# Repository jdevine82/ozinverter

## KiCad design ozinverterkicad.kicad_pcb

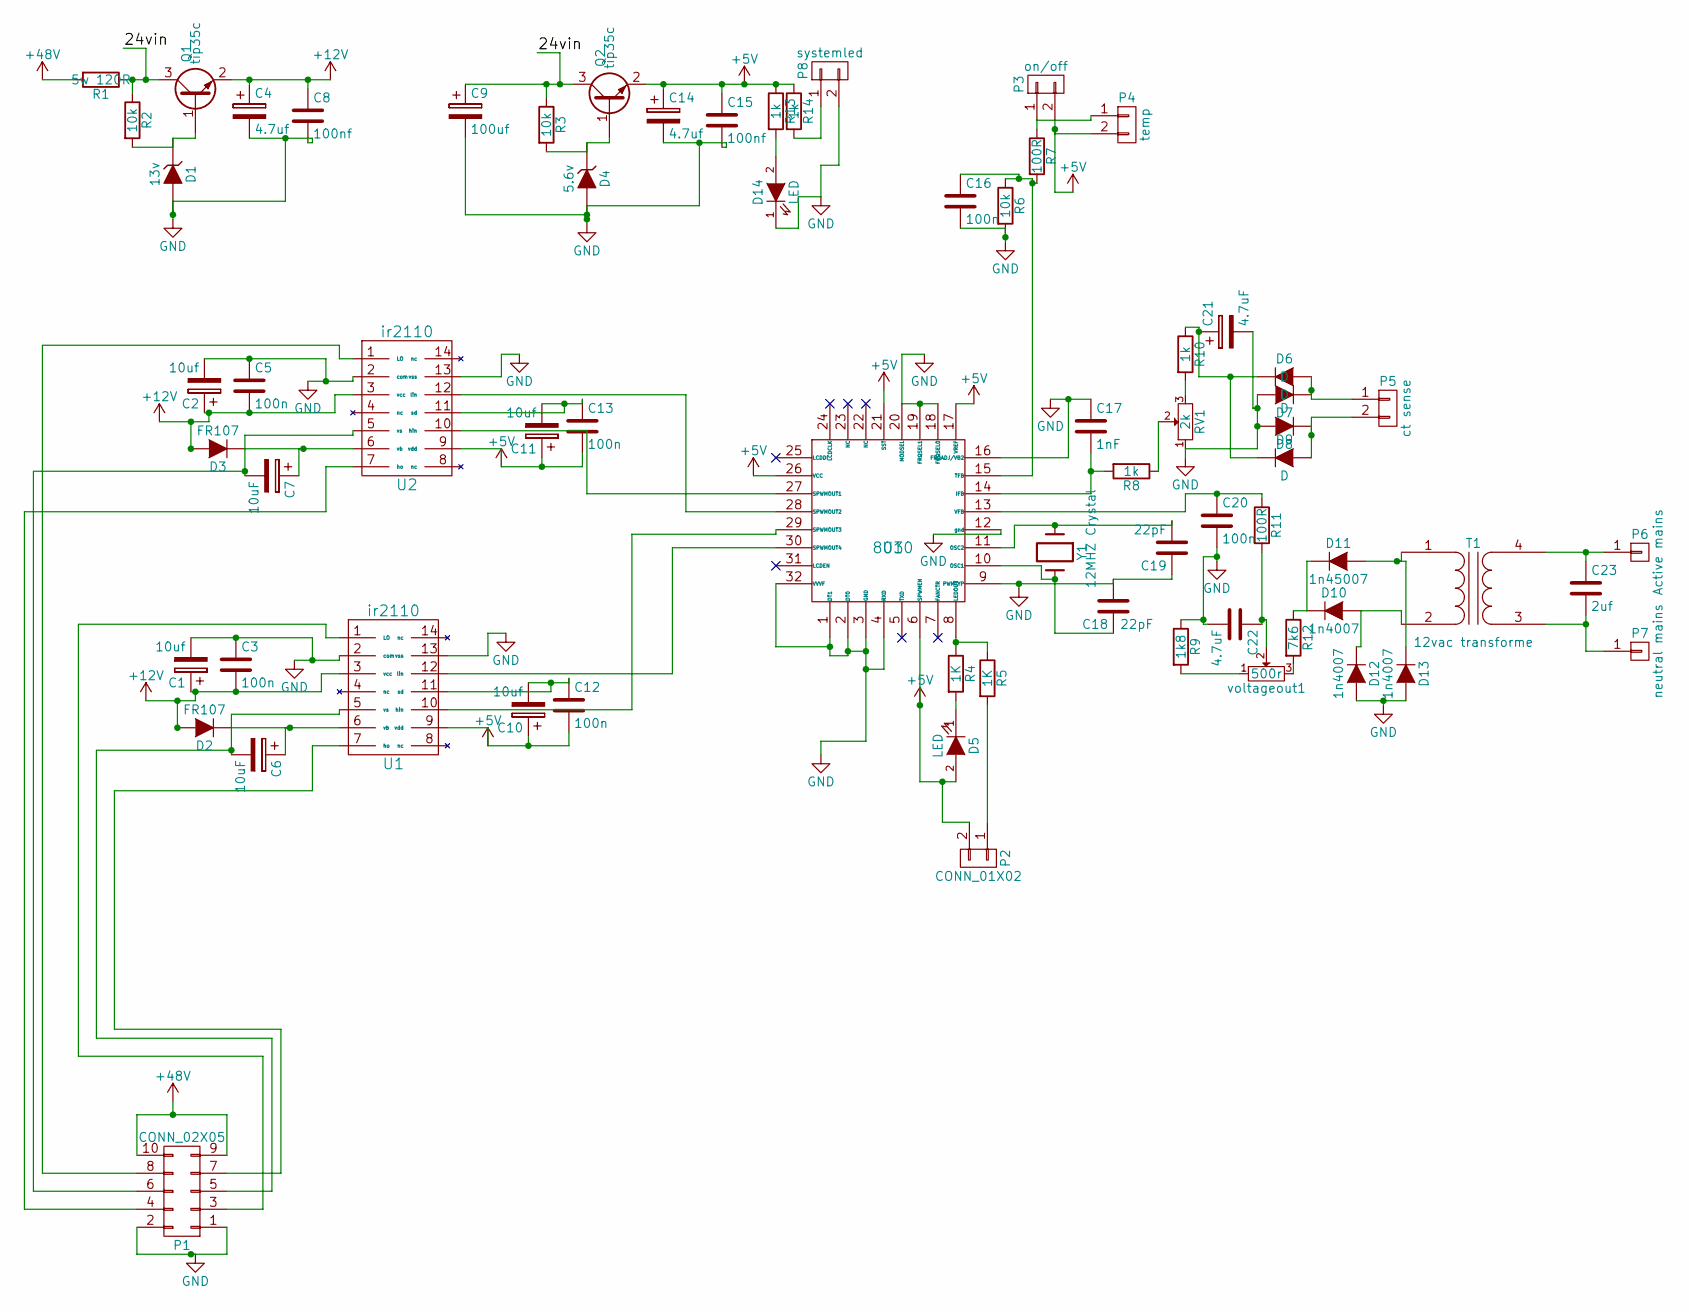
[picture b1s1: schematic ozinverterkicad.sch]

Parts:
C1, C2: 10uf; C_Radial_D5_L6_P2.5
C3, C5, C12, C13, C16, C20: 100n; C_Rect_L7_W2.5_P5
C4, C14: 4.7uf; C_Radial_D5_L6_P2.5
C6, C7: 10uF; C_Radial_D5_L6_P2.5
C8, C15: 100nf; C_Rect_L7_W2.5_P5
C9: 100uf; C_Radial_D6.3_L11.2_P2.5
C10, C11: 10uf; C_Radial_D5_L11_P2.5
C17: 1nF; C_Rect_L7_W2.5_P5
C18, C19: 22pF; C_Disc_D3_P2.5
C21, C22: 4.7uF; C_Radial_D5_L6_P2.5
C23: 2uf; C_Radial_D5_L6_P2.5
D1: 13v; Diode_DO-41_SOD81_Vertical_AnodeUp
D2, D3: FR107; Diode_DO-41_SOD81_Vertical_AnodeUp
D4: 5.6v; Diode_DO-41_SOD81_Vertical_AnodeUp
D5, D14: LED; LED-5MM
D6, D7, D8, D9: D; Diode_DO-41_SOD81_Vertical_AnodeUp
D10, D12, D13: 1n4007; Diode_DO-41_SOD81_Vertical_AnodeUp
D11: 1n45007; Diode_DO-41_SOD81_Vertical_AnodeUp
P1: CONN_02X05; IDC_Header_Straight_10pins
P2: CONN_01X02; Molex_KK-6410-02_02x2.54mm_Straight
P3: on/off; Molex_KK-6410-02_02x2.54mm_Straight
P4: temp; Molex_KK-6410-02_02x2.54mm_Straight
P5: ct sense; Molex_KK-6410-02_02x2.54mm_Straight
P6: Active mains; 1pin
P7: neutral mains; 1pin
P8: systemled; Molex_KK-6410-02_02x2.54mm_Straight
Q1, Q2: tip35c; TO-247_Vertical_Neutral123
R1: 5w 120R; Resistor_Horizontal_RM30mm
R2, R3, R6: 10k; Resistor_Horizontal_RM7mm
R4, R5: 1K; Resistor_Horizontal_RM7mm
R7, R11: 100R; Resistor_Horizontal_RM7mm
R8, R10, R13, R14: 1k; Resistor_Horizontal_RM7mm
R9: 1k8; Resistor_Horizontal_RM7mm
R12: 7k6; Resistor_Horizontal_RM7mm
RV1: 2k; RV2X4
T1: 12vac transforme; 3wtransformer
U1, U2: ir2110; DIP-14_W7.62mm
U3: 8010; DIP-32_W15.24mm
Y1: 12MHZ Crystal; Crystal_HC48-U_Vertical
voltageout1: 500r; RV2X4

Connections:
+5V: C10.1, C11.1, C12.2, C13.2, C14.1, C15.1, D5.2 (A), P2.2, P3.2, P4.2, Q2.2 (E), R13.1, R14.1, U1.9 (vdd), U2.9 (vdd), U3.6 (SPWMEN), U3.17 (VREF), U3.21 (SST), U3.26 (VCC)
+12V: C1.1, C2.1, C3.2, C4.1, C5.2, C8.1, D2.2 (A), D3.2 (A), Q1.2 (E), U1.3 (vcc), U2.3 (vcc)
+48V: P1.9, P1.10, R1.2
/24vin: C9.1, Q1.3 (C), Q2.3 (C), R1.1, R2.1, R3.1
GND: C1.2, C2.2, C3.1, C4.2, C5.1, C8.2, C9.2, C14.2, C15.2, C16.2, C17.1, C18.2, C19.1, C20.2, C21.2, C22.2, D1.2 (A), D4.2 (A), D7.2 (A), D8.2 (A), D12.2 (A), D13.2 (A), D14.1 (K), P1.1, P1.2, P8.2, R6.2, R9.1, RV1.1, U1.2 (com), U1.13 (vss), U2.2 (com), U2.13 (vss), U3.1 (DT1), U3.2 (DT0), U3.3 (GND), U3.4 (RXD), U3.9 (PWMTYP), U3.12 (gnd), U3.16 (FRQADJ/VB2), U3.18 (FRQSEL0), U3.19 (FRQSEL1), U3.20 (MODSEL), U3.32 (VVVF)
unnamed: C6.1, D2.1 (K), U1.6 (vb)
unnamed: C6.2, P1.5, U1.5 (vs)
unnamed: C7.1, D3.1 (K), U2.6 (vb)
unnamed: C7.2, P1.6, U2.5 (vs)
unnamed: C10.2, C12.1, U1.11 (sd)
unnamed: C11.2, C13.1, U2.11 (sd)
unnamed: C16.1, R6.1, R7.2, U3.15 (TFB)
unnamed: C17.2, R8.2, U3.14 (IFB)
unnamed: C18.1, U3.10 (OSC1), Y1.2
unnamed: C19.2, U3.11 (OSC2), Y1.1
unnamed: C20.1, R11.1, U3.13 (VFB)
unnamed: C21.1, D6.1 (K), D9.1 (K), R10.1
unnamed: C22.1, R11.2, voltageout1.2
unnamed: C23.1, P6.1, T1.4 (SB)
unnamed: C23.2, P7.1, T1.3 (SA)
unnamed: D1.1 (K), Q1.1 (B), R2.2
unnamed: D4.1 (K), Q2.1 (B), R3.2
unnamed: D5.1 (K), R4.2
unnamed: D6.2 (A), D7.1 (K), P5.1
unnamed: D8.1 (K), D9.2 (A), P5.2
unnamed: D10.1 (K), D11.1 (K), R12.1
unnamed: D10.2 (A), D12.1 (K), T1.2 (AB)
unnamed: D11.2 (A), D13.1 (K), T1.1 (AA)
unnamed: D14.2 (A), R13.2
unnamed: P1.3, U1.1 (LO)
unnamed: P1.4, U2.7 (ho)
unnamed: P1.7, U1.7 (ho)
unnamed: P1.8, U2.1 (LO)
unnamed: P2.1, R5.2
unnamed: P3.1, P4.1, R7.1
unnamed: P8.1, R14.2
unnamed: R4.1, R5.1, U3.8 (LEDOUT)
unnamed: R8.1, RV1.2
unnamed: R9.2, voltageout1.1
unnamed: R10.2, RV1.3
unnamed: R12.2, voltageout1.3
unnamed: U1.10 (hin), U3.29 (SPWMOUT3)
unnamed: U1.12 (lin), U3.30 (SPWMOUT4)
unnamed: U2.10 (hin), U3.27 (SPWMOUT1)
unnamed: U2.12 (lin), U3.28 (SPWMOUT2)

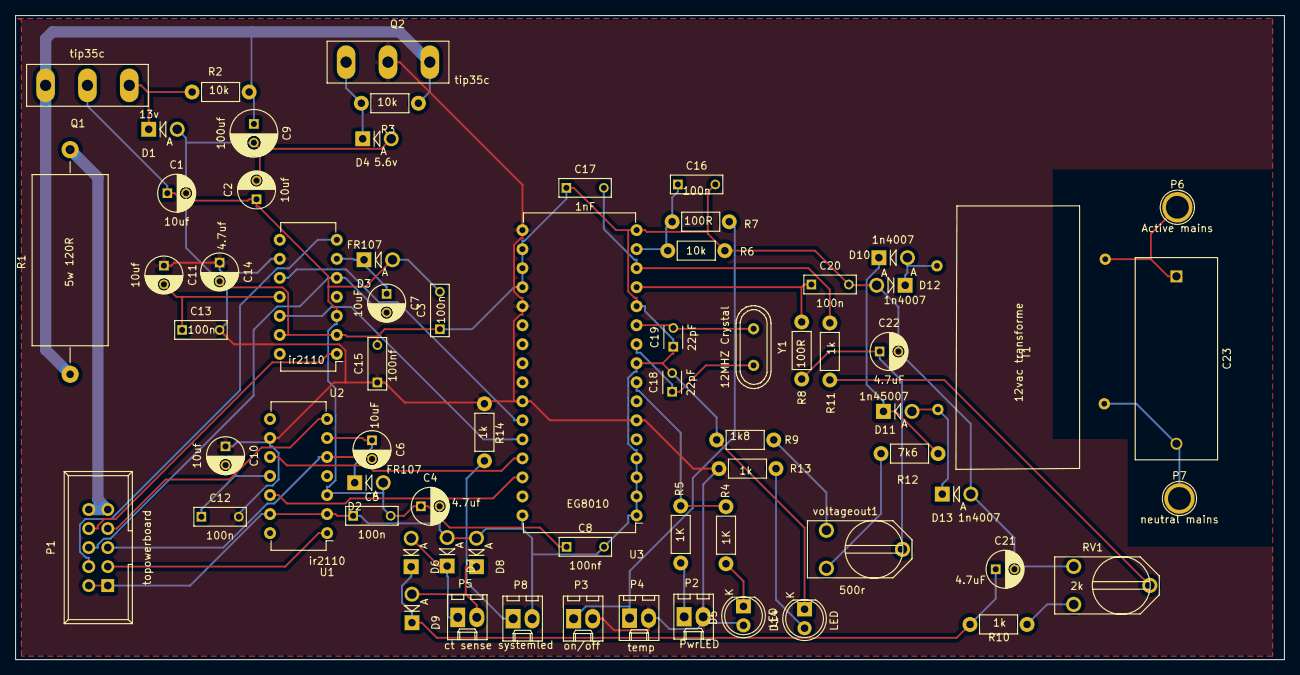
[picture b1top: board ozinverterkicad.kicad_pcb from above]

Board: 2 copper layers, 169.4 x 86.0 mm, 68 parts (0 on the bottom side), 45 nets.

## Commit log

2016-09-04 added about
2016-09-04 added picture files of board
2016-09-04 added schematic pdf
2017-08-08 reworked with connector changes
2017-08-08 added schematic
